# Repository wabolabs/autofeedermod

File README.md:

# Autofeeder Controller

Drop-in PCB replacement for a timed chicken feed dispenser. ESP32-C6 based with Matter/ESPHome, local standalone operation, motor control, CAN bus, RTC timekeeping, and optional GPS sync.

## Features

- **MCU**: ESP32-C6-Zero (Matter, WiFi 6, Thread, BLE 5) — socketed via 2×9 2.54mm headers + 7 pogo pins
- **Display**: SSD1306 128×64 SPI OLED with full menu system (status, schedules, settings, GPS, manual feed)
- **Motor**: DRV8871 H-bridge for 4VDC auger motor
- **Power**: 18650 Li-ion with TP4056 charger + DW01A/FS8205A battery protection + TPS63031 buck-boost to 3.3V
- **RTC**: DS3231 module (I2C) with CR2032 backup for offline timekeeping
- **GPS**: NEO-6M/8M module header (UART) for offline RTC time sync
- **CAN Bus**: SN65HVD230 via USB-C SBU pins
- **USB-C**: 5V charging + CAN sideband on SBU pins
- **Buttons**: 6 tactile switches (GP0–GP5) for menu navigation
- **Standalone operation**: Schedules stored in NVS, RTC keeps time without network, full local control via screen and buttons

## Project Structure

```
hardware/kicad/          — KiCad design files (generated)
  ├── autofeeder.kicad_sch      — Generated schematic
  ├── autofeeder.kicad_pcb      — Generated PCB (autorouted + verified)
  ├── autofeeder.kicad_pro      — KiCad project settings
  ├── sheet_specs/autofeeder.py — Python schematic generator
  └── autofeeder_pcb.py         — Python PCB pipeline (place, route, pour, verify, export)
hardware/symbols/         — Custom KiCad symbol library
hardware/footprints/      — Custom KiCad footprints (ESP32-C6-Zero socket, OLED module)
firmware/esphome/         — ESPHome configuration
docs/                     — BOM, pinout, mechanical specs
fabrication/              — Gerbers, drill, BOM, CPL (for JLCPCB)
tools/sch_gen/            — KiCad S-expression generation library
```

## Pin Assignments

See [docs/pinout.md](docs/pinout.md) for full GPIO table.

Key assignments:
- GP0–GP5: Buttons (individual GPIOs)
- GPIO19/20: Motor control (TX/RX repurposed)
- GP14/15/18/12: Display SPI (DC on GP12 via pogo pin)
- GP21/22: CAN bus
- GP6: Battery monitor ADC
- GP13/23: I2C for DS3231 RTC
- GP7/8: UART for GPS module

## Standalone Operation

The controller runs independently of Home Assistant/ESPHome:

- **RTC**: DS3231 keeps time with coin cell backup during power loss
- **Schedules**: Up to 4 daily feeding times stored in ESP32 NVS
- **Display**: Full menu system — status, manual feed, schedule list, time set, GPS status, settings
- **Buttons**: POWER (back), TIMER (cycle), MANUAL (feed), SETTINGS (confirm/toggle), UP/DOWN (adjust)
- **GPS**: Optional module for offline time synchronization
- **Matter**: When network is available, schedules can also be managed via Home Assistant

## Build

### Schematic
```bash
PYTHONPATH=tools python3 hardware/kicad/sheet_specs/autofeeder.py
```

### PCB
```bash
# Requires KiCad 9.0+ and Freerouting on PATH
PYTHONPATH=tools python3 hardware/kicad/autofeeder_pcb.py
```

### Firmware
```bash
cd firmware/esphome
esphome run autofeeder.yaml
```

## BOM

See [docs/bom.md](docs/bom.md) for full bill of materials.

### Required additions (not on main board)
- DS3231 RTC module (ZS-042) with CR2032 cell
- NEO-6M/7M/8M GPS module (optional)
- 7× pogo pins 0.9mm × 11mm (for Zero bottom-edge pads)

## License

CERN Open Hardware Licence Version 2 - Weakly Reciprocal (CERN-OHL-W-2.0)

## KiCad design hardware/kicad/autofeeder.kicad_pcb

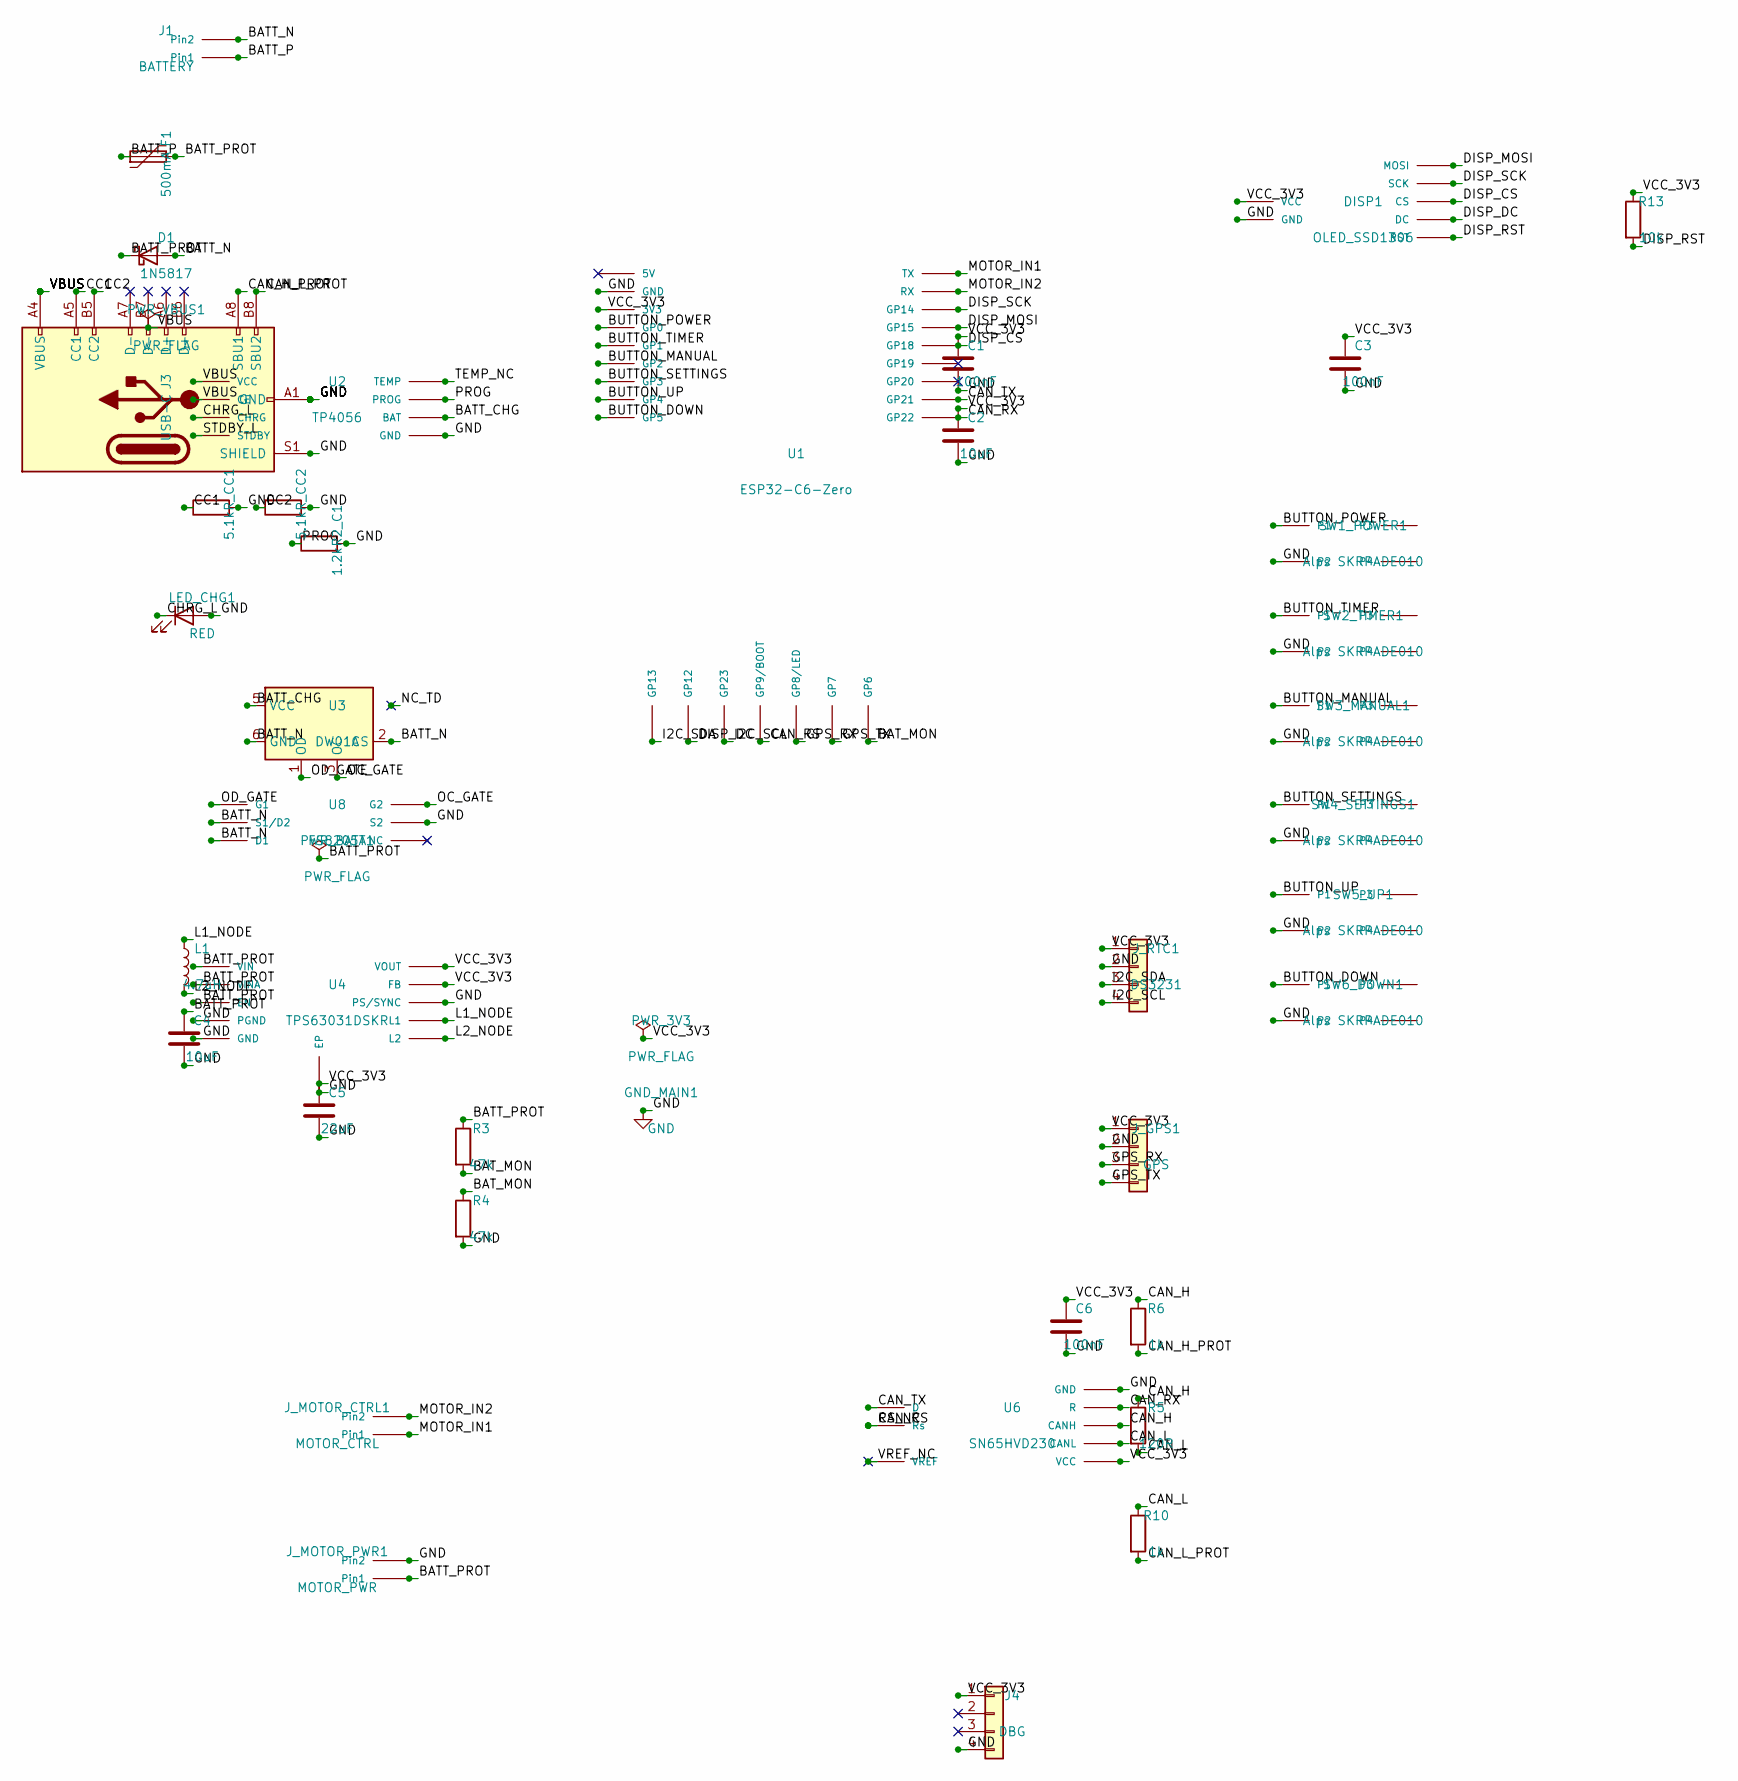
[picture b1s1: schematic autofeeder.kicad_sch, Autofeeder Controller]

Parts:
C1, C3, C6: 100nF; C_0603_1608Metric
C2, C4: 10uF; C_0805_2012Metric
C5: 22uF; C_0805_2012Metric
D1: 1N5817; D_DO-41_SOD81_P10.16mm_Horizontal
DISP1: OLED_SSD1306; OLED_1.3in_SSD1306_SPI
F1: 500mA; Fuse_1812_4532Metric
GND_MAIN1: GND
J1: BATTERY; JST_XH_B2B-XH-A_1x02_P2.50mm_Vertical
J3: USB-C; USB_C_Receptacle_HRO_TYPE-C-31-M-12
J4: DBG; PinHeader_1x04_P2.54mm_Vertical
J_GPS1: GPS; PinHeader_1x04_P2.54mm_Vertical
J_MOTOR_CTRL1: MOTOR_CTRL; JST_XH_B2B-XH-A_1x02_P2.50mm_Vertical
J_MOTOR_PWR1: MOTOR_PWR; JST_XH_B2B-XH-A_1x02_P2.50mm_Vertical
J_RTC1: DS3231; PinHeader_1x04_P2.54mm_Vertical
L1: 4.7uH; L_0805_2012Metric
LED_CHG1: RED; LED_0603_1608Metric
PWR_3V3: PWR_FLAG
PWR_BATT1: PWR_FLAG
PWR_VBUS1: PWR_FLAG
R2_C1: 1.2k; R_0603_1608Metric
R3, R4: 47k; R_0603_1608Metric
R5: 120R; R_0603_1608Metric
R6, R10: 1k; R_0603_1608Metric
R13: 10k; R_0603_1608Metric
R_CC1, R_CC2: 5.1k; R_0603_1608Metric
SW1_POWER1, SW2_TIMER1, SW3_MANUAL1, SW4_SETTINGS1, SW5_UP1, SW6_DOWN1: Alps SKRPADE010; SW_Push_1P1T_NO_CK_KMR2
U1: ESP32-C6-Zero; ESP32_C6_Zero
U2: TP4056; SOIC-8_3.9x4.9mm_P1.27mm
U3: DW01A; SOT-23-6_Handsoldering
U4: TPS63031DSKR; WSON-10-1EP_2.5x2.5mm_P0.5mm_EP1.2x2mm
U6: SN65HVD230; SOIC-8_3.9x4.9mm_P1.27mm
U8: FS8205A; SOT-23-6_Handsoldering

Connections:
/BATT_CHG: U2.5 (BAT), U3.5 (VCC)
/BATT_N: D1.2 (A), J1.2 (Pin2), U3.2 (CS), U3.6 (GND), U8.2 (S1/D2), U8.3 (D1)
/BATT_P: F1.1, J1.1 (Pin1)
/BATT_PROT: C4.1, D1.1 (K), F1.2, J_MOTOR_PWR1.1 (Pin1), PWR_BATT1.1, R3.1, U4.5 (VIN), U4.6 (EN), U4.8 (VINA)
/BAT_MON: R3.2, R4.1, U1.25 (GP6)
/BUTTON_DOWN: SW6_DOWN1.1, U1.9 (GP5)
/BUTTON_MANUAL: SW3_MANUAL1.1, U1.6 (GP2)
/BUTTON_POWER: SW1_POWER1.1, U1.4 (GP0)
/BUTTON_SETTINGS: SW4_SETTINGS1.1, U1.7 (GP3)
/BUTTON_TIMER: SW2_TIMER1.1, U1.5 (GP1)
/BUTTON_UP: SW5_UP1.1, U1.8 (GP4)
/CAN_H: R5.1, R6.1, U6.7 (CANH)
/CAN_H_PROT: J3.A8 (SBU1), R6.2
/CAN_L: R5.2, R10.1, U6.6 (CANL)
/CAN_L_PROT: J3.B8 (SBU2), R10.2
/CAN_RS: U1.22 (GP9/BOOT), U6.8 (Rs)
/CAN_RX: U1.18 (GP22), U6.4 (R)
/CAN_TX: U1.17 (GP21), U6.1 (D)
/CC1: J3.A5 (CC1), R_CC1.1
/CC2: J3.B5 (CC2), R_CC2.1
/CHRG_L: LED_CHG1.1 (K), U2.1 (CHRG)
/DISP_CS: DISP1.3 (CS), U1.14 (GP18)
/DISP_DC: DISP1.4 (DC), U1.20 (GP12)
/DISP_MOSI: DISP1.7 (MOSI), U1.13 (GP15)
/DISP_RST: DISP1.5 (RST), R13.2
/DISP_SCK: DISP1.6 (SCK), U1.12 (GP14)
/GPS_RX: J_GPS1.3, U1.23 (GP8/LED)
/GPS_TX: J_GPS1.4, U1.24 (GP7)
/I2C_SCL: J_RTC1.4, U1.21 (GP23)
/I2C_SDA: J_RTC1.3, U1.19 (GP13)
/L1_NODE: L1.1, U4.4 (L1)
/L2_NODE: L1.2, U4.2 (L2)
/MOTOR_IN1: J_MOTOR_CTRL1.1 (Pin1), U1.10 (TX)
/MOTOR_IN2: J_MOTOR_CTRL1.2 (Pin2), U1.11 (RX)
/OC_GATE: U3.3 (OC), U8.4 (G2)
/OD_GATE: U3.1 (OD), U8.1 (G1)
/PROG: R2_C1.1, U2.2 (PROG)
/STDBY_L: U2.8 (STDBY)
/TEMP_NC: U2.6 (TEMP)
/VBUS: J3.A4 (VBUS), J3.A9 (VBUS), J3.B4 (VBUS), J3.B9 (VBUS), PWR_VBUS1.1, U2.4 (VCC), U2.7 (CE)
/VCC_3V3: C1.1, C2.1, C3.1, C5.1, C6.1, DISP1.1 (VCC), J4.1, J_GPS1.1, J_RTC1.1, PWR_3V3.1, R13.1, U1.3 (3V3), U4.1 (VOUT), U4.10 (FB), U6.3 (VCC)
/VREF_NC: U6.5 (VREF)
GND: C1.2, C2.2, C3.2, C4.2, C5.2, C6.2, DISP1.2 (GND), GND_MAIN1.1, J3.A1 (GND), J3.A12 (GND), J3.B1 (GND), J3.B12 (GND), J3.S1 (SHIELD), J4.4, J_GPS1.2, J_MOTOR_PWR1.2 (Pin2), J_RTC1.2, LED_CHG1.2 (A), R2_C1.2, R4.2, R_CC1.2, R_CC2.2, SW1_POWER1.2, SW2_TIMER1.2, SW3_MANUAL1.2, SW4_SETTINGS1.2, SW5_UP1.2, SW6_DOWN1.2, U1.2 (GND), U2.3 (GND), U4.3 (PGND), U4.7 (PS/SYNC), U4.9 (GND), U4.11 (EP), U6.2 (GND), U8.5 (S2)

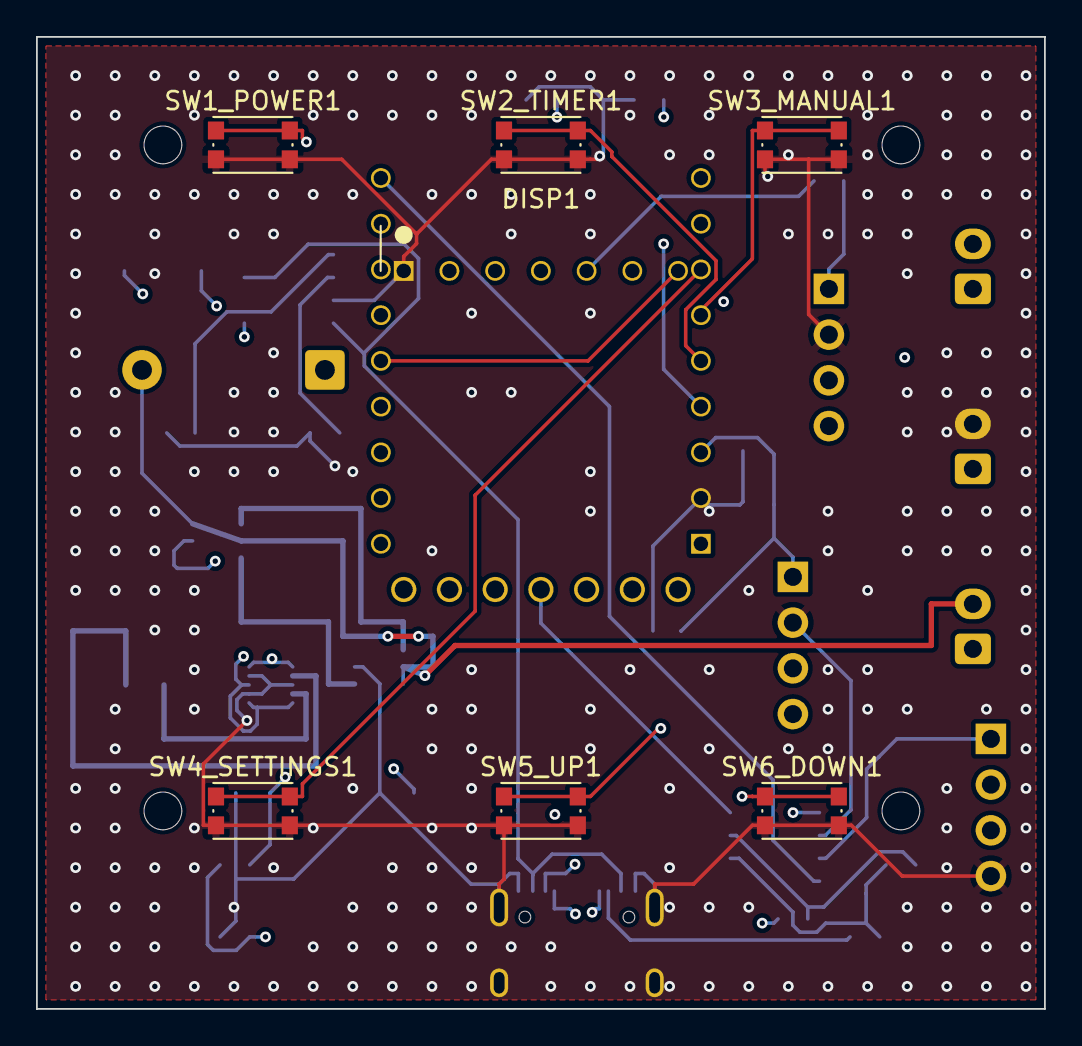
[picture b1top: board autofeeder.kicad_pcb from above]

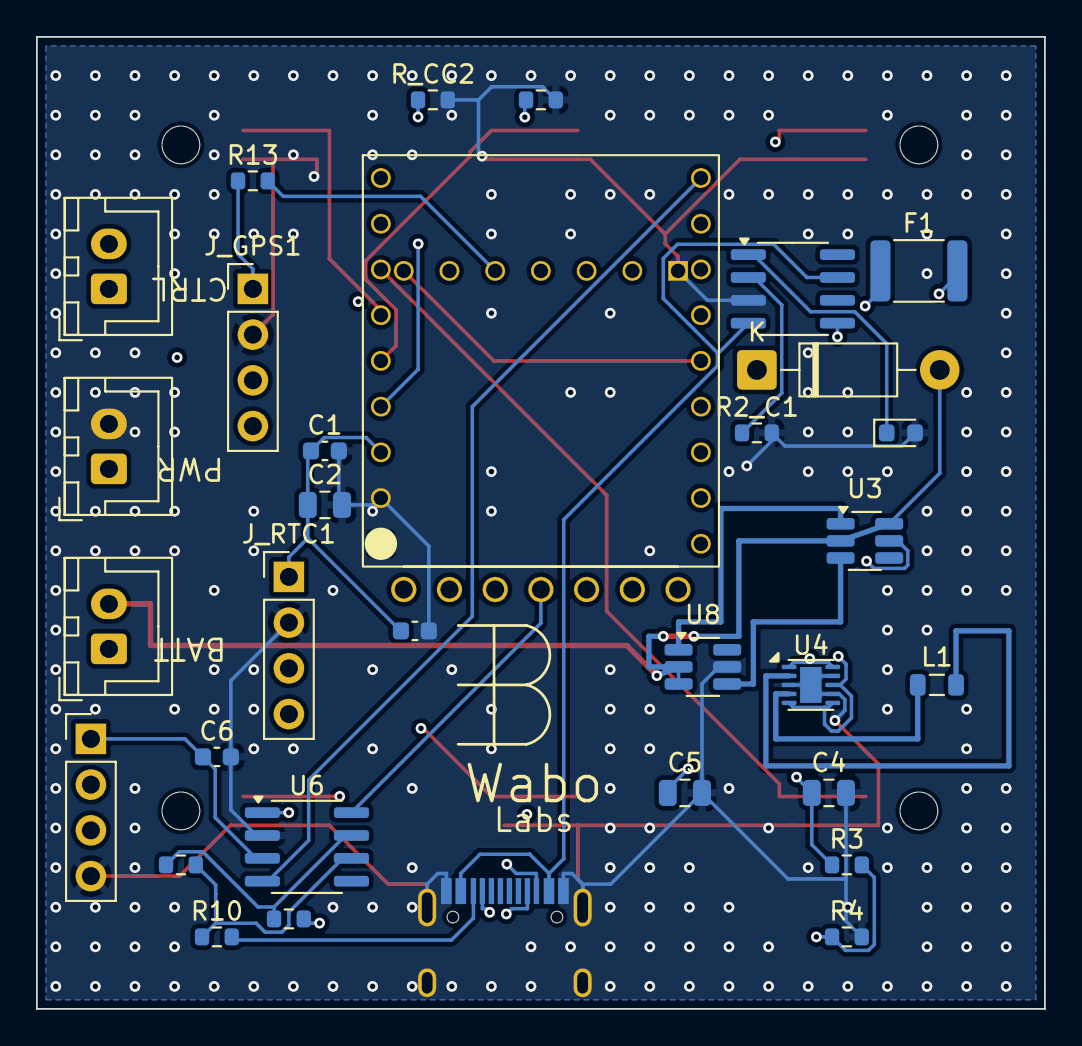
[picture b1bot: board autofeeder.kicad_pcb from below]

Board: 4 copper layers, 56.0 x 54.0 mm, 44 parts (33 on the bottom side), 40 nets.

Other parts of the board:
H1, H2, H3, H4: MountingHole_2.1mm_NPTH
WABO_LOGO1: Wabo_Labs_Logo

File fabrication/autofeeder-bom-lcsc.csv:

Comment,Designator,Footprint,LCSC Part#,Qty,Notes
"TP4056 Li-ion Charger SOIC-8","U2","SOIC-8_3.9x4.9mm_P1.27mm","C382139",1,"LCSC stock: OK"
"DW01A Li-ion Protection IC SOT-23-6","U3","SOT-23-6","C18164398",1,"LCSC stock: OK"
"FS8205A Dual NMOS SOT-23-6","U8","SOT-23-6","C2830320",1,"LCSC stock: OK"
"TPS63031DSKR Buck-Boost 3.3V WSON-10","U4","WSON-10-1EP_2.5x2.5mm_P0.5mm","C15516",1,"LCSC stock: OK"
"SN65HVD230DR CAN Transceiver SOIC-8","U6","SOIC-8_3.9x4.9mm_P1.27mm","C12084",1,"LCSC stock: OK"
"1N5817 Schottky Diode DO-41","D1","D_DO-41_SOD81_P10.16mm_Horizontal","C507852",1,"LCSC stock: OK"
"RED LED 0603 (Everlight 19-219/R6C)","LED_CHG1","LED_0603_1608Metric","C2994782",1,"Everlight — in stock"
"PTC Resettable Fuse 500mA 15V 1812","F1","Fuse_1812_4532Metric","C151169",1,"LCSC stock: OK"
"SKRPADE010 Tactile Switch 4x4mm SMD","SW1_POWER1,SW2_TIMER1,SW3_MANUAL1,SW4_SETTINGS1,SW5_UP1,SW6_DOWN1","SW_Push_1P1T_NO_CK_KMR2","C127488",6,"Alps SKRPADE010 or equiv CK KMR2"
"TYPE-C-31-M-12 USB-C Receptacle 16P","J3","USB_C_Receptacle_HRO_TYPE-C-31-M-12","C165948",1,"HRO connector"
"100nF 50V X7R 0603","C1,C3,C6","C_0603_1608Metric","C14663",3,"Decoupling caps"
"10uF 25V X7R 0805","C2,C4","C_0805_2012Metric","C3039694",2,"Bulk decoupling + input cap"
"22uF 10V X5R 0805","C5","C_0805_2012Metric","C29277",1,"TPS63031 output cap"
"4.7uH 600mA 0805 Inductor (TDK MLZ2012N4R7LTD25)","L1","L_0805_2012Metric","C404767",1,"TDK — 600mA, in stock"
"1.2kΩ 1% 0603","R2_C1","R_0603_1608Metric","C22765",1,"TP4056 PROG resistor (1A charge)"
"47kΩ 1% 0603","R3,R4","R_0603_1608Metric","C25819",2,"Battery voltage divider (47k/47k)"
"10kΩ 1% 0603","R13","R_0603_1608Metric","C25804",1,"DISP_RST pull-up"
"120Ω 1% 0603","R5","R_0603_1608Metric","C22787",1,"CAN bus termination"
"1kΩ 1% 0603","R6,R10","R_0603_1608Metric","C21190",2,"CAN_H/L series protection"
"5.1kΩ 1% 0603","R_CC1,R_CC2","R_0603_1608Metric","C23186",2,"USB-C CC pull-downs"
"JST XH B2B-XH-A 2-pin Vertical 2.5mm","J1,J_MOTOR_CTRL1,J_MOTOR_PWR1","JST_XH_B2B-XH-A_1x02_P2.50mm_Vertical","C158012",3,"Battery + motor connectors"
"Pin Header 1x4 2.54mm Vertical","J4,J_RTC1,J_GPS1","PinHeader_1x04_P2.54mm_Vertical","C42431787",3,"Debug + RTC + GPS module headers"
"Pogo Pin 0.9mm x 11mm ~2mm Stroke","P1,P2,P3,P4,P5,P6,P7","THT","——",7,"NOT on LCSC — source from DigiKey/Mill-Max"
"ESP32-C6-Zero Module (Waveshare)","U1","ESP32_C6_Zero","——",1,"Customer-supplied — Waveshare module"
"OLED 1.3in SSD1306/SH1106 SPI 128x64","DISP1","OLED_1.3in_SSD1306_SPI","——",1,"Customer-supplied — 7-pin SPI module"
"MX1508 Dual H-Bridge Motor Driver Module","——","External breakout board","——",1,"Customer-supplied — external module"
"DS3231 RTC Module (ZS-042) with CR2032","——","PinHeader_1x04_P2.54mm_Vertical","——",1,"Customer-supplied — I2C RTC module"
"NEO-6M/7M/8M GPS Module","——","PinHeader_1x04_P2.54mm_Vertical","——",1,"Optional — customer-supplied GPS module"
"18650 Li-ion Cell 3.7V Protected","——","——","——",1,"Customer-supplied — battery"
"CR2032 3V Lithium Coin Cell","——","——","——",1,"Customer-supplied — RTC backup battery"

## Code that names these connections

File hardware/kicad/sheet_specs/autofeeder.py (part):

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
    # J1: Battery JST XH
    j1 = s.add("J1", "autofeeder:JST_XH_2P", "BATTERY", at=(30, 15), footprint=FP_JST_XH)
    label_pins(j1, {"1": "BATT_P", "2": "BATT_N"})

    # F1: PTC fuse
    f1 = s.add("F1", "Device:Polyfuse", "500mA", at=(30, 30), rotation=90,
               footprint="Fuse:Fuse_1812_4532Metric")
    label_pins(f1, {"1": "BATT_P", "2": "BATT_PROT"})

    # D1: Schottky protection
    d1 = s.add("D1", "Device:D_Schottky", "1N5817", at=(30, 45),
               footprint="Diode_THT:D_DO-41_SOD81_P10.16mm_Horizontal")
    label_pins(d1, {"1": "BATT_PROT", "2": "BATT_N"})

    # J3: USB-C
    j3 = s.add("J3", "Connector:USB_C_Receptacle_USB2.0_16P",
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    s.no_connect(j3.pin_xy("B7"))
    # SBU1/2 → CAN_H_PROT/L_PROT via series resistors (handled below)
    # (no direct labels here — the CAN series protection resistors R6/R10
    #  connect via CAN_H_PROT / CAN_L_PROT labels at the USB-C side)

    # U2: TP4056 charger
    u2 = s.add("U2", "autofeeder:TP4056", "TP4056", at=(55, 65), footprint=FP_SOIC8)
    label_pins(u2, {"4": "VBUS", "3": "GND", "5": "BATT_CHG",
                    "2": "PROG", "1": "CHRG_L", "7": "VBUS", "6": "TEMP_NC", "8": "STDBY_L"})

    # R2: PROG resistor (1.2k for 1A charge)
    r2 = s.add("R2_C", "Device:R", "1.2k", at=(55, 85), rotation=90, footprint=FP_R_0603)
    label_pins(r2, {"1": "PROG", "2": "GND"})

    # LED2: Charge indicator (RED, CHRG = active low)
    led2 = s.add("LED_CHG", "Device:LED", "RED", at=(35, 95), footprint="LED_SMD:LED_0603_1608Metric")
    label_pins(led2, {"1": "CHRG_L", "2": "GND"})
    # Note: CHRG is open-drain, so LED cathode goes to GND, anode to CHRG
    # Meaning: LED illuminates when CHRG pulls low (charging)

    # U3: DW01A battery protection IC (SOT-23-6, hand-solderable)
    u3 = s.add("U3", "Battery_Management:DW01A", "DW01A", at=(55, 110),
               footprint=FP_SOT23_6_HS)
    label_pins(u3, {"5": "BATT_CHG", "6": "BATT_N", "1": "OD_GATE",
                    "3": "OC_GATE", "2": "BATT_N", "4": "NC_TD"})
    s.no_connect(u3.pin_xy("4"))

    # U8: FS8205A dual NMOS (SOT-23-6) — charge/discharge protection FETs driven by DW01A
    u8 = s.add("U8", "autofeeder:FS8205A", "FS8205A", at=(55, 125),
               footprint=FP_SOT23_6_HS)
    label_pins(u8, {"1": "OD_GATE", "4": "OC_GATE",
                    "2": "BATT_N", "3": "BATT_N", "5": "GND"})
    s.no_connect(u8.pin_xy("6"))

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    # Fixed 3.3V output — no feedback resistors needed. Pinout per DSK package:
    # 1=VOUT, 2=L2, 3=PGND, 4=L1, 5=VIN, 6=EN, 7=PS/SYNC, 8=VINA, 9=GND, 10=FB, 11=EP
    u4 = s.add("U4", "autofeeder:TPS63031DSKR", "TPS63031DSKR", at=(55, 150), footprint=FP_WSON10_TPS63031)
    label_pins(u4, {"5": "BATT_PROT",   # VIN
                    "8": "BATT_PROT",   # VINA
                    "6": "BATT_PROT",   # EN (tie to input to always enable)
                    "3": "GND",         # PGND
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
    # L1: 4.7uH inductor for TPS63031 L1-L2 (SW node to VOUT)
    l1 = s.add("L1", "Device:L", "4.7uH", at=(35, 145), footprint=FP_L_0805)
    label_pins(l1, {"1": "L1_NODE", "2": "L2_NODE"})

    # C4, C5: TPS63031 input/output caps
    c4 = s.add("C4", "Device:C", "10uF", at=(35, 155), footprint=FP_C_0805)
    label_pins(c4, {"1": "BATT_PROT", "2": "GND"})
    c5 = s.add("C5", "Device:C", "22uF", at=(55, 165), footprint=FP_C_0805)
    label_pins(c5, {"1": "VCC_3V3", "2": "GND"})

    # R3, R4: Battery voltage divider (BAT_MON)
    r3 = s.add("R3", "Device:R", "47k", at=(75, 170), footprint=FP_R_0603)
    r4 = s.add("R4", "Device:R", "47k", at=(75, 180), footprint=FP_R_0603)
    label_pins(r3, {"1": "BATT_PROT", "2": "BAT_MON"})
    label_pins(r4, {"1": "BAT_MON", "2": "GND"})

    # ===== MCU SECTION =====

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    label_pins(u1, {"3": "VCC_3V3", "2": "GND"})
    s.no_connect(u1.pin_xy("1"))      # 5V: unused — main board USB-C powers TP4056
    # Buttons: GP0-GP5 on left rail (all ADC-capable, 6 buttons)
    label_pins(u1, {"4": "BUTTON_POWER", "5": "BUTTON_TIMER",
                    "6": "BUTTON_MANUAL", "7": "BUTTON_SETTINGS",
                    "8": "BUTTON_UP", "9": "BUTTON_DOWN"})
    # Motor control on TX/RX pads (right rail top 2) — repurposed from UART programming.
    # Programming is done via the Zero's own USB-C (tucked inside enclosure) or boot-ROM mode.
    label_pins(u1, {"10": "MOTOR_IN1", "11": "MOTOR_IN2"})
    # Display SPI: GP14=SCK, GP15=MOSI, GP18=CS
    # DISP_DC moved to bottom pad GP12 to resolve pin conflict with MOTOR_IN1 (both on GPIO19)
    label_pins(u1, {"12": "DISP_SCK", "13": "DISP_MOSI",
                    "14": "DISP_CS"})
    # GPIO19 (pad 15) and GPIO20 (pad 16) are NC — conflicts with MOTOR pins resolved
    s.no_connect(u1.pin_xy("15"))
    s.no_connect(u1.pin_xy("16"))
    # CAN bus: GP21=TX, GP22=RX
    label_pins(u1, {"17": "CAN_TX", "18": "CAN_RX"})
    # Bottom edge pads (19-25) — accessed via pogo pins soldered into through-holes.
    # These contact the Zero module's bottom castellated pads.
    # Pad 20 (GP12): DISP_DC (moved from conflicted GPIO19)
    # Pad 25 (GP6):  BAT_MON (moved from conflicted GPIO20, ADC-capable)
    # Pad 19 (GP13): I2C_SDA (DS3231 RTC)
    # Pad 21 (GP23): I2C_SCL (DS3231 RTC)
    # Pad 24 (GP7):  GPS_TX (UART TX to GPS module)
    # Pad 23 (GP8):  GPS_RX (UART RX from GPS module, strapping — input only)
    # Pad 22 (GP9):  NC (BOOT strapping, avoid)
    label_pins(u1, {"20": "DISP_DC", "25": "BAT_MON",
                    "19": "I2C_SDA", "21": "I2C_SCL",
                    "24": "GPS_TX", "23": "GPS_RX"})
    # GP9/BOOT — strapping, used to drive CAN_RS (SN65HVD230 standby)
    # HIGH during sleep = CAN standby mode (~1µA); LOW during active = CAN high-speed
    label_pins(u1, {"22": "CAN_RS"})

    # C1, C2: ESP32 decoupling
    c1 = s.add("C1", "Device:C", "100nF", at=(145, 60), footprint=FP_C_0603)
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
    # J_MOTOR_CTRL: MX1508 logic inputs from ESP32
    j_mtr_ctrl = s.add("J_MOTOR_CTRL", "autofeeder:JST_XH_2P", "MOTOR_CTRL", at=(55, 210), footprint=FP_JST_XH)
    label_pins(j_mtr_ctrl, {"1": "MOTOR_IN1", "2": "MOTOR_IN2"})

    # J_MOTOR_PWR: MX1508 power supply (battery + ground)
    j_mtr_pwr = s.add("J_MOTOR_PWR", "autofeeder:JST_XH_2P", "MOTOR_PWR", at=(55, 230), footprint=FP_JST_XH)
    label_pins(j_mtr_pwr, {"1": "BATT_PROT", "2": "GND"})

    # ===== CAN SECTION =====

    # U6: SN65HVD230 CAN transceiver
    u6 = s.add("U6", "autofeeder:SN65HVD230", "SN65HVD230", at=(150, 210), footprint=FP_SOIC8)
    label_pins(u6, {"1": "CAN_TX", "4": "CAN_RX", "8": "RS_NC",
                    "7": "CAN_H", "6": "CAN_L",
                    "5": "VREF_NC", "3": "VCC_3V3", "2": "GND"})
    s.no_connect(u6.pin_xy("5"))
    # RS pin (8) driven by GP9 for standby mode during sleep
    label_pins(u6, {"8": "CAN_RS"})

    # R5: CAN termination (120R, selectable via solder jumper)
    r5 = s.add("R5", "Device:R", "120R", at=(170, 210), footprint=FP_R_0603)
    label_pins(r5, {"1": "CAN_H", "2": "CAN_L"})

    # R6, R10: CAN series protection
    r6 = s.add("R6", "Device:R", "1k", at=(170, 195), footprint=FP_R_0603)
    r10 = s.add("R10", "Device:R", "1k", at=(170, 225), footprint=FP_R_0603)
    label_pins(r6, {"1": "CAN_H", "2": "CAN_H_PROT"})
    label_pins(r10, {"1": "CAN_L", "2": "CAN_L_PROT"})
    label_at("CAN_H_PROT", j3.pin_xy("A8"))
    label_at("CAN_L_PROT", j3.pin_xy("B8"))

    # C6: CAN decoupling
    c6 = s.add("C6", "Device:C", "100nF", at=(160, 195), footprint=FP_C_0603)
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    # Pinout: VCC, GND, SDA, SCL. Module has onboard pull-ups and CR2032 holder.
    j_rtc = s.add("J_RTC", "Connector_Generic:Conn_01x04", "DS3231", at=(170, 145),
                  footprint=FP_PIN_1x4)
    label_pins(j_rtc, {"1": "VCC_3V3", "2": "GND", "3": "I2C_SDA", "4": "I2C_SCL"})

    # ===== GPS SECTION =====

    # J_GPS: 4-pin header for NEO-6M/NEO-8M GPS module
    # Pinout: VCC, GND, GPS_RX (module TX→ESP), GPS_TX (ESP→module RX)
    j_gps = s.add("J_GPS", "Connector_Generic:Conn_01x04", "GPS", at=(170, 170),
                  footprint=FP_PIN_1x4)
    label_pins(j_gps, {"1": "VCC_3V3", "2": "GND", "3": "GPS_RX", "4": "GPS_TX"})

    # ===== DISPLAY PULL-UPS =====

    # R13: DISP_RST pull-up — SSD1306 RST pin held high; no GPIO needed for hardware reset
    r13 = s.add("R13", "Device:R", "10k", at=(240, 40), footprint=FP_R_0603)
    label_pins(r13, {"1": "VCC_3V3", "2": "DISP_RST"})

    # STATUS LED: replaced by the WS2812B RGB LED built into the ESP32-C6-Zero (on IO8/pad 12).
    # No discrete LED or current-limit resistor needed on the main board.
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    label_at("VBUS", pwr_vbus.pin_xy("1"))

    pwr_batt = s.add("PWR_BATT", "power:PWR_FLAG", "PWR_FLAG", at=(55, 130))
    label_at("BATT_PROT", pwr_batt.pin_xy("1"))

    pwr_3v3 = s.add("PWR_3V3", "power:PWR_FLAG", "PWR_FLAG", at=(100, 155))
    label_at("VCC_3V3", pwr_3v3.pin_xy("1"))
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
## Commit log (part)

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2026-06-02 Initial autofeeder controller board design
    ESP32-C6 based PCB replacement for chicken feed dispenser.
    - KiCad project with full schematic (USB-C + 18650 battery + CAN)
    - Symbol library for ESP32-C6, TP4056, TPS63802, DRV8871, SN65HVD230
    - ESPHome firmware skeleton with Matter support
    - CERN-OHL-W-2.0 open hardware license
2026-06-02 Add Python PCB generation pipeline for autofeeder controller
    - Python S-expression library (tools/sch_gen/) for KiCad file generation
    - Declarative Sheet builder with component placement, wire stubs, net labels
    - Symbol library for custom parts (JST, OLED, Alps switch, ICs)
    - Full schematic generator: 41 components, power/MCU/motor/CAN/display
    - Generated KiCad 9 schematic with board outline (56x54mm)
    - PCB generation pipeline script (headless placement + routing)
2026-06-02 Fix custom symbol library format
    - Add (exclude_from_sim no) at top level of each symbol
    - Add (pin_numbers (hide yes)) field
    - Fix bare hide to (hide yes) format
    - Strip (id N) from property fields in cache
2026-06-03 Snapshot current design (ESP32-C6-Zero, RT6150A buck-boost, FS8205A protection)
    - Switch from ESP32-C6-WROOM module to Waveshare ESP32-C6-Zero (socketed)
    - Replace TPS63802 (QFN) with RT6150A (SOT-23-6, hand-solderable)
    - Split DW01A+FS8205A into separate U3/U8 symbols (SOT-23-6)
    - Add gerber/drill/CPL fabrication output
    - Add mounting holes and OLED SPI display footprint
    - Generate schematic + PCB from Python pipeline scripts
2026-06-04 Add RTC, GPS, pogo pin support and standalone firmware
    - Fix GPIO19/GPIO20 pin conflicts: move DISP_DC to GP12 (bottom pad),
    BAT_MON to GP6 (bottom pad)
    - Add J_RTC header: DS3231 RTC module on I2C (GP13/GP23)
    - Add J_GPS header: NEO-6M/8M GPS module on UART (GP7/GP8)
    - Enlarge bottom edge pads 19-25 to 1.0mm drill for 0.9mm pogo pins
    - Rewrite ESPHome firmware: DS3231 RTC time, GPS, 6-page display menu,
2026-06-05 Add standalone firmware with RTC, GPS, OLED UI, and menu system
    - ESPHome firmware (autofeeder.yaml): RTC timekeeping with DS1307, SNTP+GPS
    fallback, SSD1306 display with clock/manual feed/schedules/GPS/Settings menu,
    6 GPIO buttons, DRV8871 motor control, battery monitoring, CAN bus
    - GPS time sync: 30s interval checks TinyGPSPlus, sets system time via
    settimeofday, persists to DS1307 via write_time()
    - Hardware: J_RTC at (28,36) back side under OLED, J_GPS at (44,14) top-right,
